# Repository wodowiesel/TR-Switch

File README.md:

# TR-Switch

The TX/RX-switch is a tool for signal sensitive or PTT switching for HAM radios incl. pcb schematics.

## DISCLAIMERS

**This is still "work-in-progress (WIP)" so I do NOT take any kind of responsibility for damages/data losses!**

**You can use this at your own risk without guarantees and put device on non conductive surface or enclosure!**

If you like the new design yo are free to share it!

Have fun :)

## HARDWARE

- 1x Custom PCB by WodoWiesel

- 1x USB-X cable for power supply

- 1x THT-SPDT relay +5V

- 3x THT-BNC female socket connector

- 1x THT-1N4001 flyback suppression diode

- 1x THT-2N3904 (TO-92) BJT transistor

- 3x THT-LED green+orange+red (tx/rx/pwr-indicator)

- 2x THT variable resistors 3-pin (~50-1kOhm)

- 1x THT-3.5mm socket (optional)

- 1x cable for PTT (optional)

- 1x enclosure/box (recommended)

- 1x Soldering iron

- Solder + flux + IPA

## SOFTWARE

No need for that.

## HOW TO USE

1. set up antenna, LNA, Transceiver and cables & adapters

2. connect PTT (optional)

3. turn on +5V power supply

4. Have Fun 73

## CREDITS

:copyright: 10/10/2023 WodoWiesel

Github (https://github.com/wodowiesel/)

Twitch (https://www.twitch.com/wodowiesel/)

Instagram (https://www.instagram.com/wodowiesel/)

YT (https://www.youtube.com/@wodowiesel/)

E-Mail (wodowiesel@quantentunnel.de)

The new design was checked by the electrical engineer theBrutzler (https://github.com/theBrutzler/)

The new optimized PCB was designed with free KiCAD software (https://www.kicad.org/)

:heavy_exclamation_mark: The PCB should be produced at a manufacturer

(like PCBWay or similar) with the RoHS lead-free option for environmental protection.

## LICENSES

- Hardware

CERN Open Hardware License Version 2 - Weakly Reciprocal

Short identifier CERN-OHL-W-2.0

[LICENSE Source](https://spdx.org/licenses/CERN-OHL-W-2.0.html)

- Software

This work is licensed under a Creative Commons Attribution-NonCommercial 3.0 Unported License.

[CCANC](http://creativecommons.org/licenses/by-nc/3.0/)

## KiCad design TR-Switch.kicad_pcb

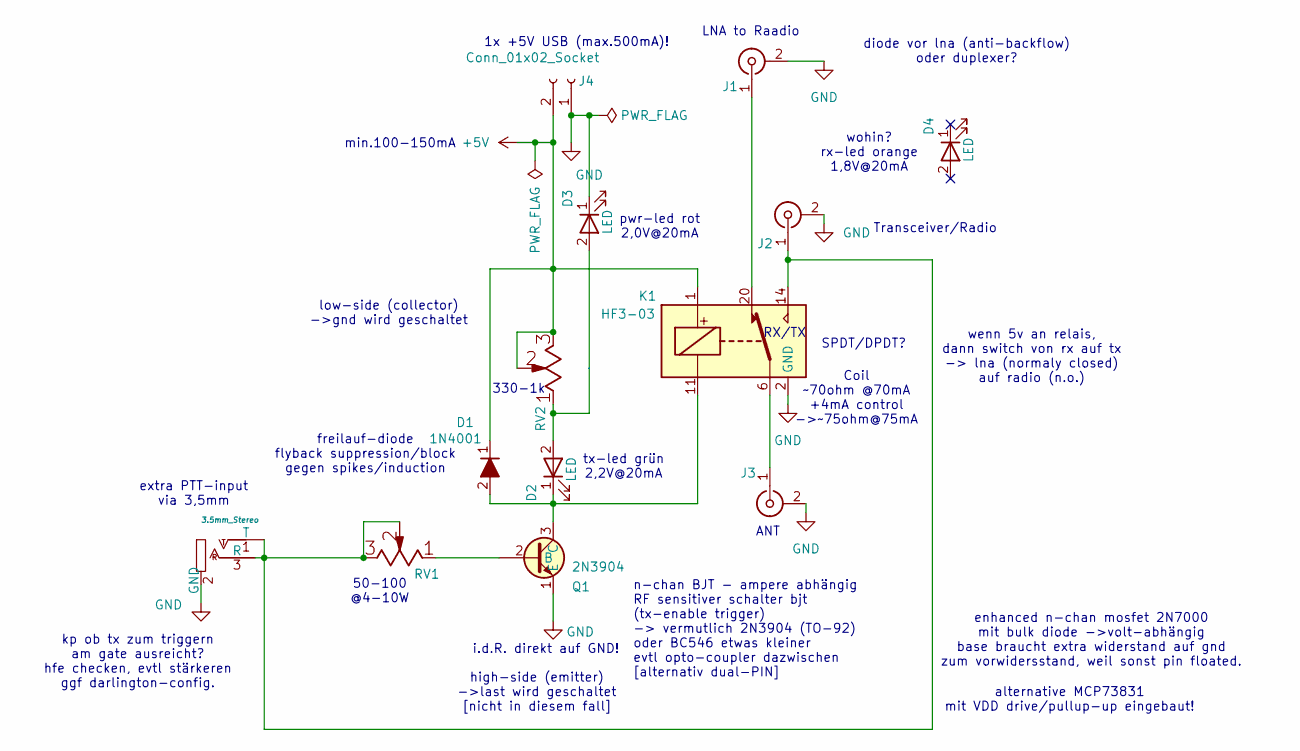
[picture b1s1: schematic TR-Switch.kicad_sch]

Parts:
D1: 1N4001; D_DO-41_SOD81_P7.62mm_Horizontal
D2, D3, D4: LED; LED_D5.0mm
J1, J2: Conn_Coaxial; SMA_Amphenol_132289_EdgeMount
J3: Conn_Coaxial; BNC_TEConnectivity_1478035_Horizontal
J4: Conn_01x02_Socket; PinSocket_1x02_P2.54mm_Vertical
J5: 3.5mm_Stereo_SymSmall_0.05; Jack_3.5mm_CUI_SJ1-3533NG_Horizontal-wodo; Part Number WQP-WQP419GR
K1: HF3-03; Relay_SPDT_AXICOM_HF3Series_75ohms_Pitch1.27mm
Q1: 2N3904; TO-92_Inline_Wide_EBC
RV1: 50Ohm; Potentiometer_Bourns_3386C_Horizontal
RV2: 1kOhm; Potentiometer_Bourns_3386C_Horizontal

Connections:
+5V: D1.1 (K), J4.2, K1.1, RV2.2 (b), RV2.3 (c)
GND: D3.1 (K), J1.2 (Ext), J2.2 (Ext), J3.2 (Ext), J4.1, J5.2 (GND), K1.2 (GND), K1.5 (GND), K1.7 (GND), K1.10 (GND), K1.12 (GND), K1.13 (GND), K1.15 (GND), K1.17 (GND), K1.19 (GND), K1.21 (GND), K1.22 (GND), Q1.1 (E)
unnamed: D1.2 (A), D2.1 (K), K1.11, Q1.3 (C)
unnamed: D2.2 (A), D3.2 (A), RV2.1 (a)
unnamed: J1.1 (In), K1.20
unnamed: J2.1 (In), J5.1 (T), J5.3 (R), K1.14, RV1.2 (b), RV1.3 (c)
unnamed: J3.1 (In), K1.6
unnamed: Q1.2 (B), RV1.1 (a)

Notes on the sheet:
Transceiver/Radio
high-side (emitter) ->last wird geschaltet [nicht in diesem fall]
alternative MCP73831 mit VDD drive/pullup-up eingebaut!
SPDT/DPDT?
diode vor lna (anti-backflow) oder duplexer?
wenn 5v an relais, dann switch von rx auf tx -> lna (normaly closed) auf radio (n.o.)
tx-led grün 2,2V@20mA
50-100 @4-10W
freilauf-diode flyback suppression/block gegen spikes/induction
enhanced n-chan mosfet 2N7000 mit bulk diode ->volt-abhängig base braucht extra widerstand auf gnd zum vorwidersstand, weil sonst pin floated.
n-chan BJT - ampere abhängig RF sensitiver schalter bjt (tx-enable trigger) -> vermutlich 2N3904 (TO-92) oder BC546 etwas kleiner evtl opto-coupler dazwischen [alternativ dual-PIN]
wohin? rx-led orange 1,8V@20mA
extra PTT-input via 3,5mm
330-1k
LNA to Raadio
i.d.R. direkt auf GND!
Coil ~70ohm @70mA +4mA control ->~75ohm@75mA
min.100-150mA
RX/TX
1x +5V USB (max.500mA)!
low-side (collector) ->gnd wird geschaltet
pwr-led rot 2,0V@20mA
kp ob tx zum triggern am gate ausreicht? hfe checken, evtl stärkeren ggf darlington-config.
ANT

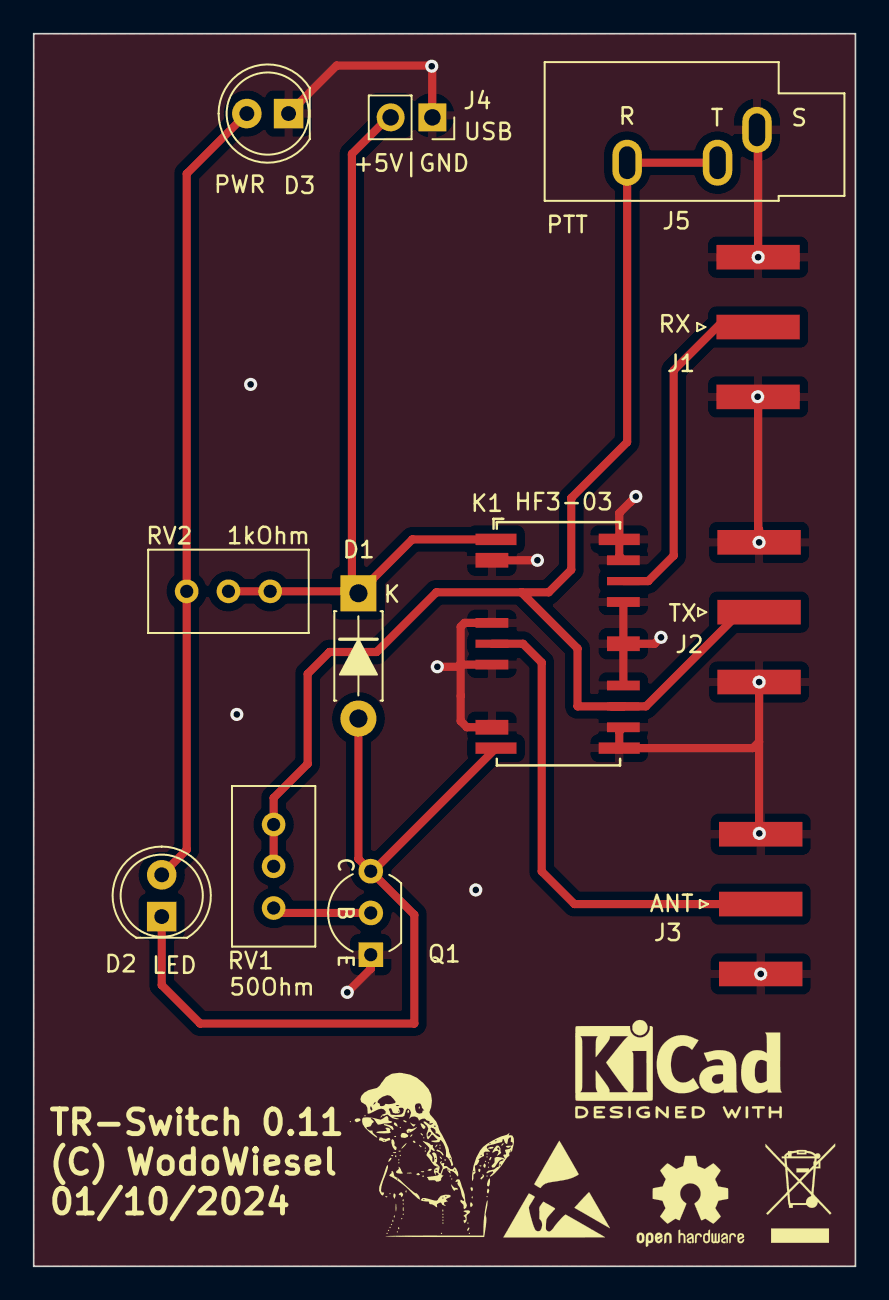
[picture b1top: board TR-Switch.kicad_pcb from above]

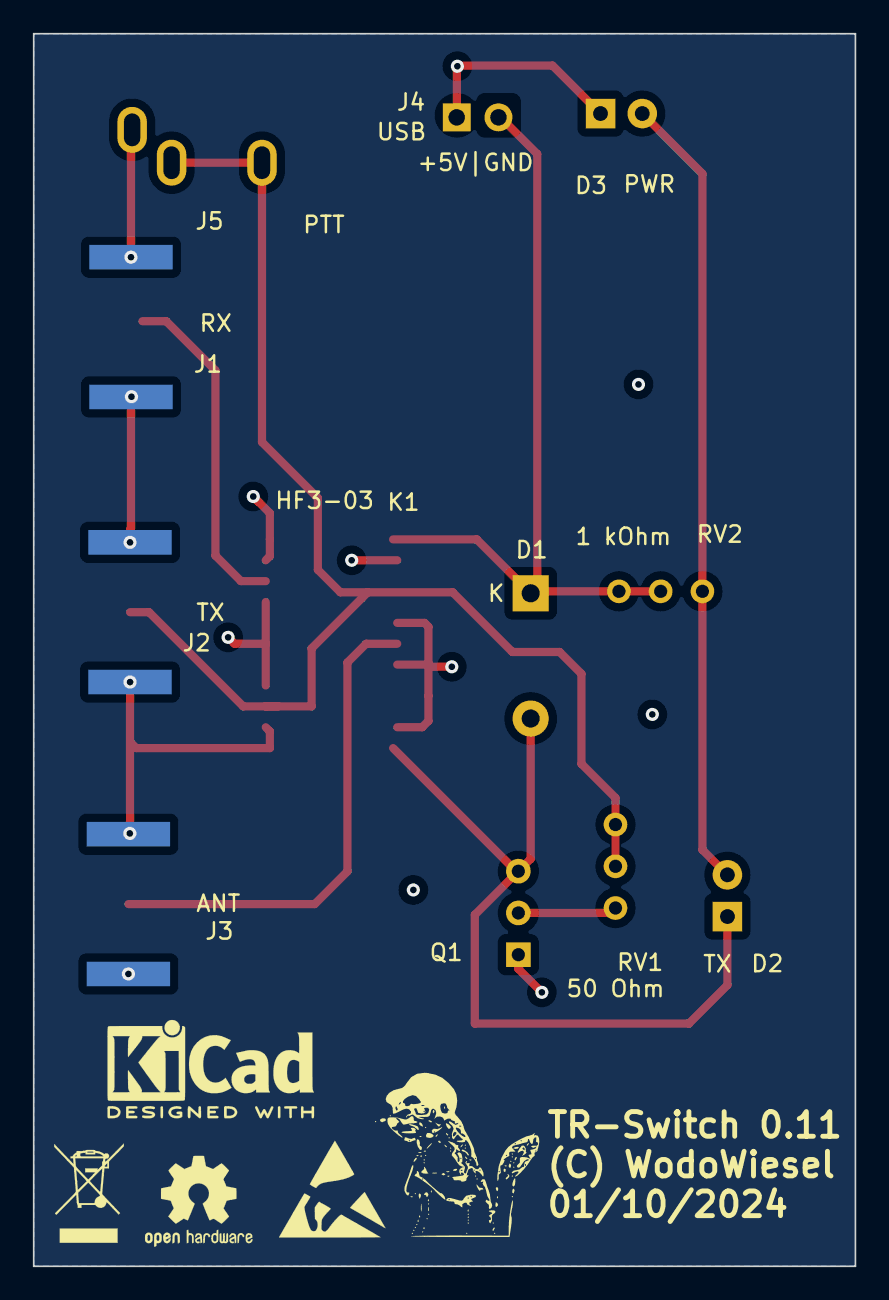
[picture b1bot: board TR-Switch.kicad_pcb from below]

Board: 2 copper layers, 50.0 x 75.0 mm, 22 parts (5 on the bottom side), 8 nets.

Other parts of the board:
G1, G11: LOGO; wiesel-logo-kicad-back-white
REF1, REF11: ESD-Logo_6.6x6mm_SilkScreen
REF2, REF22: OSHW-Logo2_7.3x6mm_SilkScreen
REF3, REF33: WEEE-Logo_4.2x6mm_SilkScreen
REF4, REF44: KiCad-Logo2_5mm_SilkScreen

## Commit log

2024-06-09 init
    init
2024-10-09 -docu + comments -new layout
2024-10-09 fix typo
